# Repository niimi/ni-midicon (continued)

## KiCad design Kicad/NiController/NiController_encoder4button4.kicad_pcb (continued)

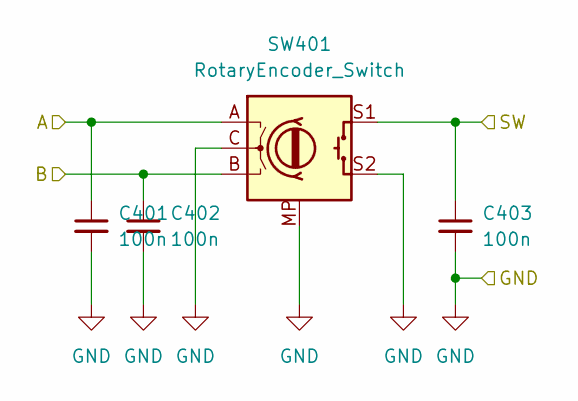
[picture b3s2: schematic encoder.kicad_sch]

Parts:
C401, C402, C403: 100n; C_0603_1608Metric
SW401: RotaryEncoder_Switch; PEC11-4xxxF-Sxxxx

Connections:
/encoder4button4/0_GPA0: C401.1, SW401.A; also elsewhere on the board
/encoder4button4/0_GPA1: C402.1, SW401.B; also elsewhere on the board
/encoder4button4/0_GPA2: C403.1, SW401.S1; also elsewhere on the board
GND: C401.2, C402.2, C403.2, SW401.C, SW401.MP, SW401.S2; also elsewhere on the board

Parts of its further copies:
C501, C502, C503, C601, C602, C603, C701, C702, C703: 100n; C_0603_1608Metric
SW501, SW601, SW701: RotaryEncoder_Switch; PEC11-4xxxF-Sxxxx

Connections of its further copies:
/encoder4button4/0_GPA3: C501.1, SW501.A; also elsewhere on the board
/encoder4button4/0_GPA4: C502.1, SW501.B; also elsewhere on the board
/encoder4button4/0_GPA5: C503.1, SW501.S1; also elsewhere on the board
/encoder4button4/0_GPA6: C601.1, SW601.A; also elsewhere on the board
/encoder4button4/0_GPA7: C602.1, SW601.B; also elsewhere on the board
/encoder4button4/0_GPB0: C603.1, SW601.S1; also elsewhere on the board
/encoder4button4/0_GPB1: C701.1, SW701.A; also elsewhere on the board
/encoder4button4/0_GPB2: C702.1, SW701.B; also elsewhere on the board
/encoder4button4/0_GPB3: C703.1, SW701.S1; also elsewhere on the board
GND: C501.2, C502.2, C503.2, C601.2, C602.2, C603.2, C701.2, C702.2, C703.2, SW501.C, SW501.MP, SW501.S2, SW601.C, SW601.MP, SW601.S2, SW701.C, SW701.MP, SW701.S2; also elsewhere on the board

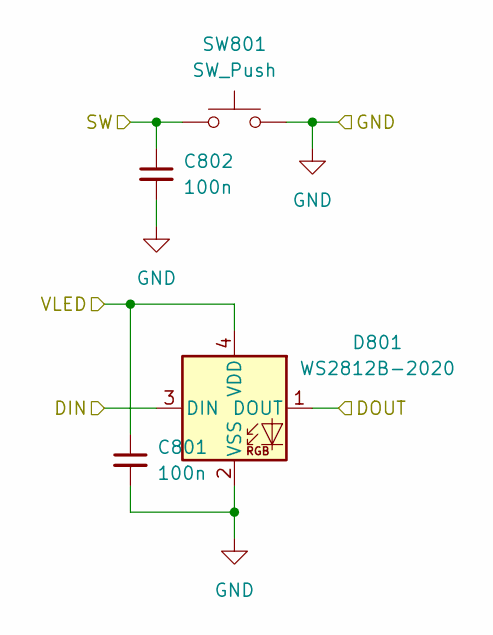
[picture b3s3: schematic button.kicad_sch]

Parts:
C801, C802: 100n; C_0603_1608Metric
D801: WS2812B-2020; LED_WS2812B-2020_PLCC4_2.0x2.0mm
SW801: SW_Push; SW_Cherry_MX_1.00u_PCB

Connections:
/encoder4button4/0_GPB4: C802.1, SW801.1; also elsewhere on the board
/encoder4button4/LED_5V: C801.1, D801.4 (VDD); also elsewhere on the board
/encoder4button4/LED_RING_DOUT: D801.3 (DIN); also elsewhere on the board
/encoder4button4/button0/DOUT: D801.1 (DOUT); also elsewhere on the board
GND: C801.2, C802.2, D801.2 (VSS), SW801.2; also elsewhere on the board

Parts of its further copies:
C901, C902, C1901, C1902, C2901, C2902: 100n; C_0603_1608Metric
D901, D1901, D2901: WS2812B-2020; LED_WS2812B-2020_PLCC4_2.0x2.0mm
SW901, SW1901, SW2901: SW_Push; SW_Cherry_MX_1.00u_PCB

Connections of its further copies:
/encoder4button4/0_GPB5: C902.1, SW901.1; also elsewhere on the board
/encoder4button4/0_GPB6: C1902.1, SW1901.1; also elsewhere on the board
/encoder4button4/0_GPB7: C2902.1, SW2901.1; also elsewhere on the board
/encoder4button4/LED_5V: C901.1, C1901.1, C2901.1, D901.4 (VDD), D1901.4 (VDD), D2901.4 (VDD); also elsewhere on the board
/encoder4button4/LED_DOUT: D2901.1 (DOUT); also elsewhere on the board
/encoder4button4/button0/DOUT: D901.3 (DIN); also elsewhere on the board
/encoder4button4/button1/DOUT: D901.1 (DOUT), D1901.3 (DIN)
/encoder4button4/button2/DOUT: D1901.1 (DOUT), D2901.3 (DIN)
GND: C901.2, C902.2, C1901.2, C1902.2, C2901.2, C2902.2, D901.2 (VSS), D1901.2 (VSS), D2901.2 (VSS), SW901.2, SW1901.2, SW2901.2; also elsewhere on the board

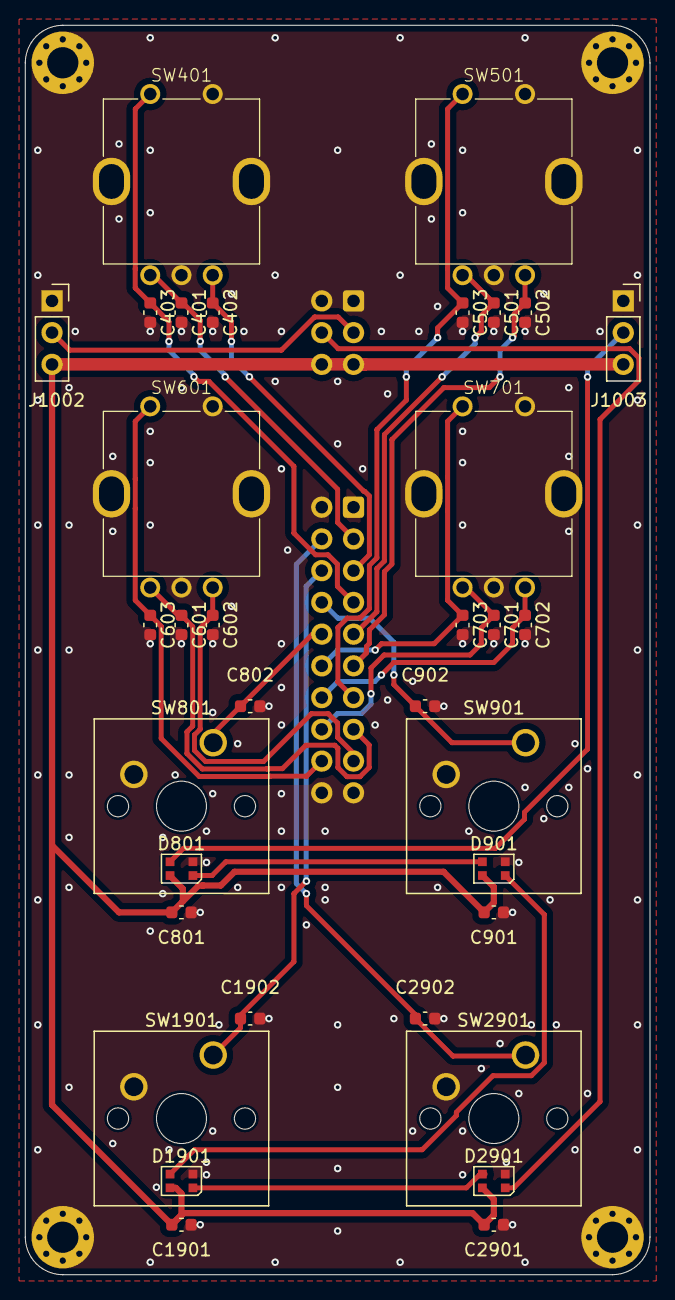
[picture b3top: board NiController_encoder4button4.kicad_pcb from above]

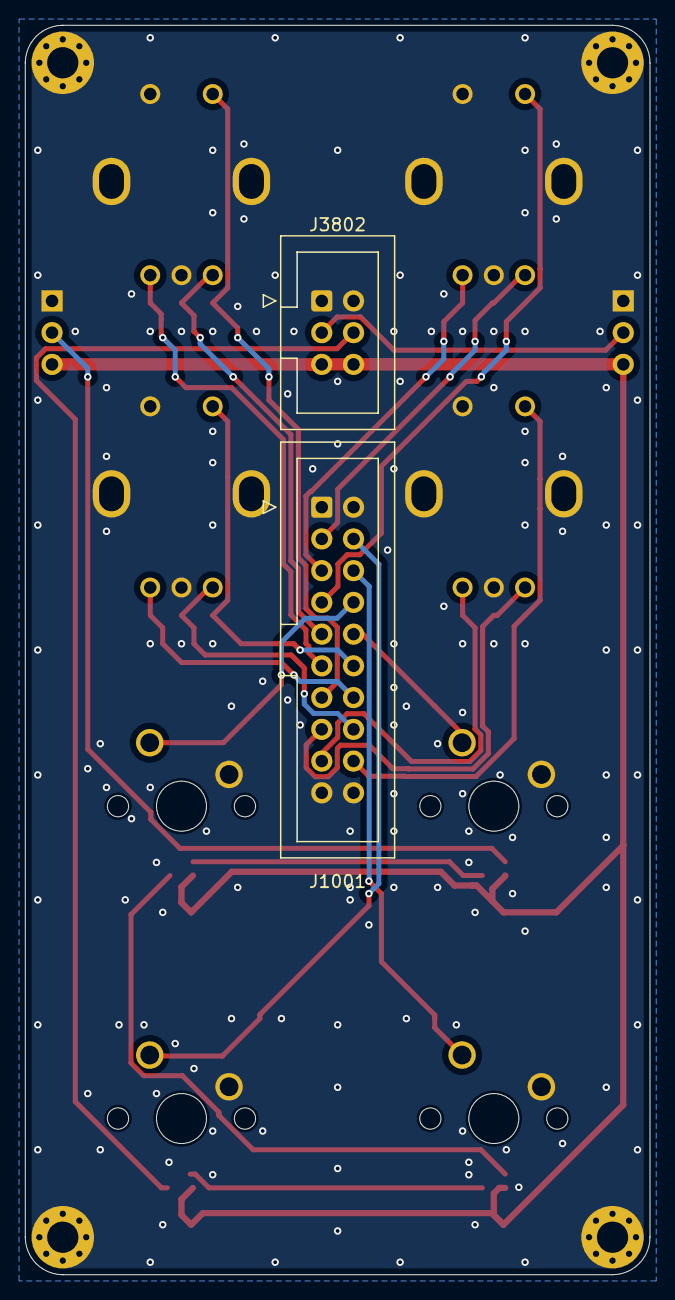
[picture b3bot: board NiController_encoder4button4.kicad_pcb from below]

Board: 2 copper layers, 50.0 x 100.0 mm, 40 parts (2 on the bottom side), 24 nets.

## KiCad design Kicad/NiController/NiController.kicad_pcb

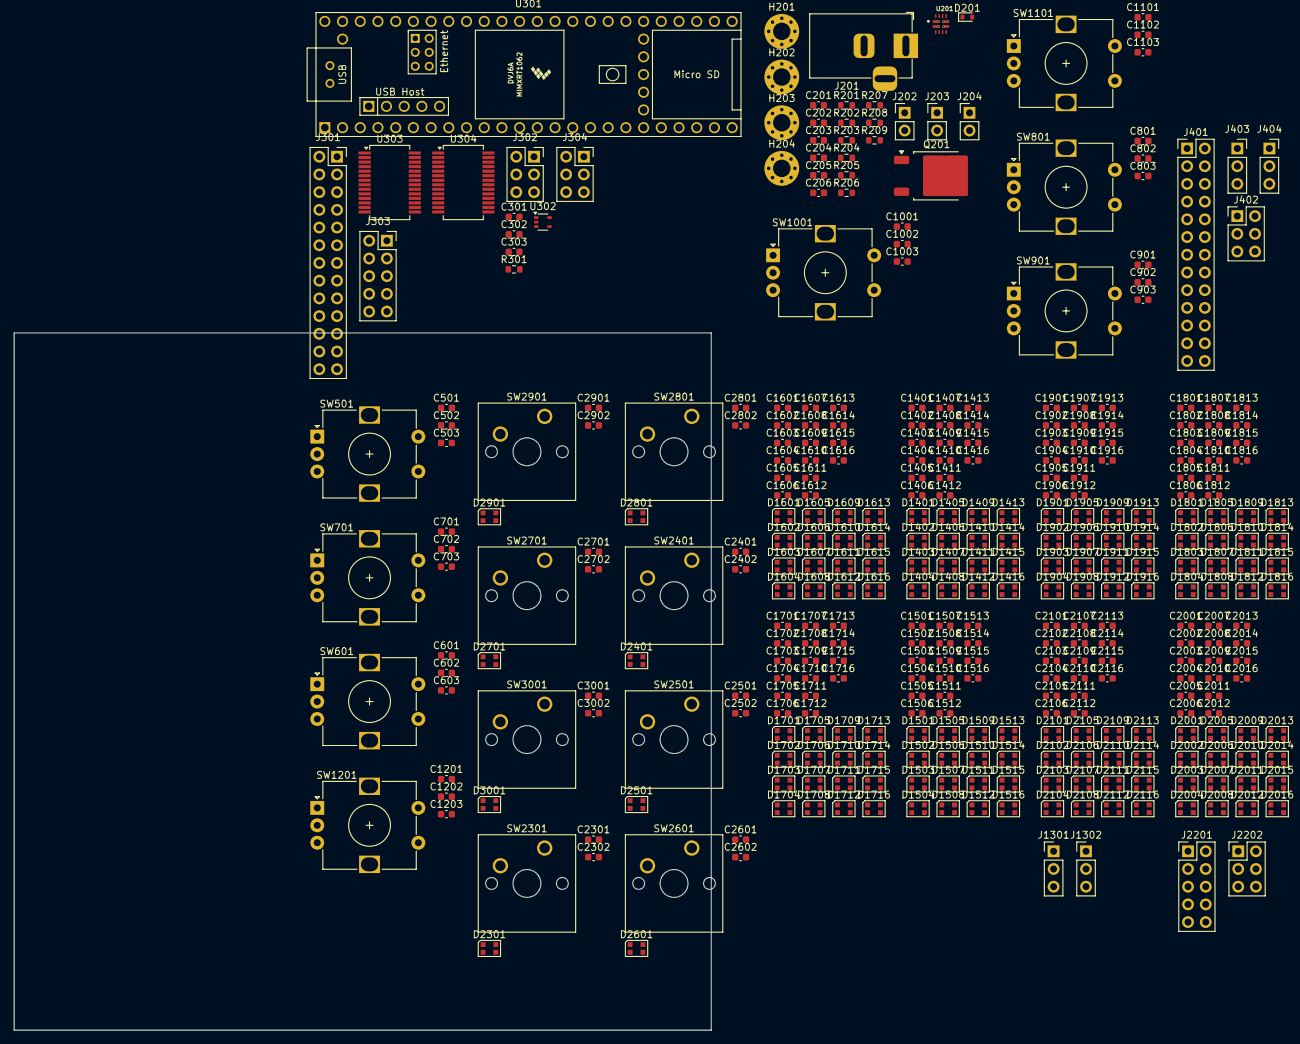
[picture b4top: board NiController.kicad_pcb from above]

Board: 2 copper layers, 100.0 x 100.0 mm, 366 parts (0 on the bottom side), 229 nets, no tracks yet.

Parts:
C201, C206: 1u; C_0603_1608Metric
C202, C203, C204, C205, C301, C302, C303, C501, C502, C503, C601, C602, C603, C701, C702, C703, C801, C802, C803, C901, C902, C903, C1001, C1002, C1003, C1101, C1102, C1103, C1201, C1202, C1203, C1401, C1402, C1403, C1404, C1405, C1406, C1407, C1408, C1409, C1410, C1411, C1412, C1413, C1414, C1415, C1416, C1501, C1502, C1503, C1504, C1505, C1506, C1507, C1508, C1509, C1510, C1511, C1512, C1513, C1514, C1515, C1516, C1601, C1602, C1603, C1604, C1605, C1606, C1607, C1608, C1609, C1610, C1611, C1612, C1613, C1614, C1615, C1616, C1701, C1702, C1703, C1704, C1705, C1706, C1707, C1708, C1709, C1710, C1711, C1712, C1713, C1714, C1715, C1716, C1801, C1802, C1803, C1804, C1805, C1806, C1807, C1808, C1809, C1810, C1811, C1812, C1813, C1814, C1815, C1816, C1901, C1902, C1903, C1904, C1905, C1906, C1907, C1908, C1909, C1910, C1911, C1912, C1913, C1914, C1915, C1916, C2001, C2002, C2003, C2004, C2005, C2006, C2007, C2008, C2009, C2010, C2011, C2012, C2013, C2014, C2015, C2016, C2101, C2102, C2103, C2104, C2105, C2106, C2107, C2108, C2109, C2110, C2111, C2112, C2113, C2114, C2115, C2116, C2301, C2302, C2401, C2402, C2501, C2502, C2601, C2602, C2701, C2702, C2801, C2802, C2901, C2902, C3001, C3002: 100n; C_0603_1608Metric
D201: D_TVS_Small; D_SOD-523
D1401, D1402, D1403, D1404, D1405, D1406, D1407, D1408, D1409, D1410, D1411, D1412, D1413, D1414, D1415, D1416, D1501, D1502, D1503, D1504, D1505, D1506, D1507, D1508, D1509, D1510, D1511, D1512, D1513, D1514, D1515, D1516, D1601, D1602, D1603, D1604, D1605, D1606, D1607, D1608, D1609, D1610, D1611, D1612, D1613, D1614, D1615, D1616, D1701, D1702, D1703, D1704, D1705, D1706, D1707, D1708, D1709, D1710, D1711, D1712, D1713, D1714, D1715, D1716, D1801, D1802, D1803, D1804, D1805, D1806, D1807, D1808, D1809, D1810, D1811, D1812, D1813, D1814, D1815, D1816, D1901, D1902, D1903, D1904, D1905, D1906, D1907, D1908, D1909, D1910, D1911, D1912, D1913, D1914, D1915, D1916, D2001, D2002, D2003, D2004, D2005, D2006, D2007, D2008, D2009, D2010, D2011, D2012, D2013, D2014, D2015, D2016, D2101, D2102, D2103, D2104, D2105, D2106, D2107, D2108, D2109, D2110, D2111, D2112, D2113, D2114, D2115, D2116, D2301, D2401, D2501, D2601, D2701, D2801, D2901, D3001: WS2812B-2020; LED_WS2812B-2020_PLCC4_2.0x2.0mm
H201, H202, H203, H204: MountingHole_Pad; MountingHole_2.5mm_Pad_Via
J201: Barrel_Jack_Switch; BarrelJack_Horizontal
J202, J203, J204: Conn_01x02; PinHeader_1x02_P2.54mm_Vertical
J301: Conn_02x13_Odd_Even; PinSocket_2x13_P2.54mm_Vertical
J302, J304: Conn_02x03_Odd_Even; PinSocket_2x03_P2.54mm_Vertical
J303: Conn_02x05_Odd_Even; PinSocket_2x05_P2.54mm_Vertical
J401: Conn_02x13_Odd_Even; PinHeader_2x13_P2.54mm_Vertical
J402, J2202: Conn_02x03_Odd_Even; PinHeader_2x03_P2.54mm_Vertical
J403, J404: Conn_01x03; PinSocket_1x03_P2.54mm_Vertical
J1301, J1302: Conn_01x03; PinHeader_1x03_P2.54mm_Vertical
J2201: Conn_02x05_Odd_Even; PinHeader_2x05_P2.54mm_Vertical
Q201: Q_PMOS_GDS; TO-252-2
R201, R203: 20.5k; R_0603_1608Metric
R202, R204, R206, R208: 5k; R_0603_1608Metric
R205: 10k; R_0603_1608Metric
R207: 15k; R_0603_1608Metric
R209: 22.1k; R_0603_1608Metric
R301: 100; R_0603_1608Metric
SW501, SW601, SW701, SW801, SW901, SW1001, SW1101, SW1201: RotaryEncoder_Switch; RotaryEncoder_Alps_EC12E-Switch_Vertical_H20mm
SW2301, SW2401, SW2501, SW2601, SW2701, SW2801, SW2901, SW3001: SW_Push; SW_Cherry_MX_1.00u_PCB
U201: TPS2121RUXR; IC_TPS2121RUXR
U301: Teensy4.1; Teensy41
U302: 74LVC1GU04; SOT-353_SC-70-5
U303, U304: MCP23S17_SS; SSOP-28_5.3x10.2mm_P0.65mm

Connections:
+5V: C1401.1, C1402.1, C1403.1, C1404.1, C1405.1, C1406.1, C1407.1, C1408.1, C1409.1, C1410.1, C1411.1, C1412.1, C1413.1, C1414.1, C1415.1, C1416.1, C1501.1, C1502.1, C1503.1, C1504.1, C1505.1, C1506.1, C1507.1, C1508.1, C1509.1, C1510.1, C1511.1, C1512.1, C1513.1, C1514.1, C1515.1, C1516.1, C1601.1, C1602.1, C1603.1, C1604.1, C1605.1, C1606.1, C1607.1, C1608.1, C1609.1, C1610.1, C1611.1, C1612.1, C1613.1, C1614.1, C1615.1, C1616.1, C1701.1, C1702.1, C1703.1, C1704.1, C1705.1, C1706.1, C1707.1, C1708.1, C1709.1, C1710.1, C1711.1, C1712.1, C1713.1, C1714.1, C1715.1, C1716.1, C1801.1, C1802.1, C1803.1, C1804.1, C1805.1, C1806.1, C1807.1, C1808.1, C1809.1, C1810.1, C1811.1, C1812.1, C1813.1, C1814.1, C1815.1, C1816.1, C1901.1, C1902.1, C1903.1, C1904.1, C1905.1, C1906.1, C1907.1, C1908.1, C1909.1, C1910.1, C1911.1, C1912.1, C1913.1, C1914.1, C1915.1, C1916.1, C2001.1, C2002.1, C2003.1, C2004.1, C2005.1, C2006.1, C2007.1, C2008.1, C2009.1, C2010.1, C2011.1, C2012.1, C2013.1, C2014.1, C2015.1, C2016.1, C2101.1, C2102.1, C2103.1, C2104.1, C2105.1, C2106.1, C2107.1, C2108.1, C2109.1, C2110.1, C2111.1, C2112.1, C2113.1, C2114.1, C2115.1, C2116.1, D1401.4 (VDD), D1402.4 (VDD), D1403.4 (VDD), D1404.4 (VDD), D1405.4 (VDD), D1406.4 (VDD), D1407.4 (VDD), D1408.4 (VDD), D1409.4 (VDD), D1410.4 (VDD), D1411.4 (VDD), D1412.4 (VDD), D1413.4 (VDD), D1414.4 (VDD), D1415.4 (VDD), D1416.4 (VDD), D1501.4 (VDD), D1502.4 (VDD), D1503.4 (VDD), D1504.4 (VDD), D1505.4 (VDD), D1506.4 (VDD), D1507.4 (VDD), D1508.4 (VDD), D1509.4 (VDD), D1510.4 (VDD), D1511.4 (VDD), D1512.4 (VDD), D1513.4 (VDD), D1514.4 (VDD), D1515.4 (VDD), D1516.4 (VDD), D1601.4 (VDD), D1602.4 (VDD), D1603.4 (VDD), D1604.4 (VDD), D1605.4 (VDD), D1606.4 (VDD), D1607.4 (VDD), D1608.4 (VDD), D1609.4 (VDD), D1610.4 (VDD), D1611.4 (VDD), D1612.4 (VDD), D1613.4 (VDD), D1614.4 (VDD), D1615.4 (VDD), D1616.4 (VDD), D1701.4 (VDD), D1702.4 (VDD), D1703.4 (VDD), D1704.4 (VDD), D1705.4 (VDD), D1706.4 (VDD), D1707.4 (VDD), D1708.4 (VDD), D1709.4 (VDD), D1710.4 (VDD), D1711.4 (VDD), D1712.4 (VDD), D1713.4 (VDD), D1714.4 (VDD), D1715.4 (VDD), D1716.4 (VDD), D1801.4 (VDD), D1802.4 (VDD), D1803.4 (VDD), D1804.4 (VDD), D1805.4 (VDD), D1806.4 (VDD), D1807.4 (VDD), D1808.4 (VDD), D1809.4 (VDD), D1810.4 (VDD), D1811.4 (VDD), D1812.4 (VDD), D1813.4 (VDD), D1814.4 (VDD), D1815.4 (VDD), D1816.4 (VDD), D1901.4 (VDD), D1902.4 (VDD), D1903.4 (VDD), D1904.4 (VDD), D1905.4 (VDD), D1906.4 (VDD), D1907.4 (VDD), D1908.4 (VDD), D1909.4 (VDD), D1910.4 (VDD), D1911.4 (VDD), D1912.4 (VDD), D1913.4 (VDD), D1914.4 (VDD), D1915.4 (VDD), D1916.4 (VDD), D2001.4 (VDD), D2002.4 (VDD), D2003.4 (VDD), D2004.4 (VDD), D2005.4 (VDD), D2006.4 (VDD), D2007.4 (VDD), D2008.4 (VDD), D2009.4 (VDD), D2010.4 (VDD), D2011.4 (VDD), D2012.4 (VDD), D2013.4 (VDD), D2014.4 (VDD), D2015.4 (VDD), D2016.4 (VDD), D2101.4 (VDD), D2102.4 (VDD), D2103.4 (VDD), D2104.4 (VDD), D2105.4 (VDD), D2106.4 (VDD), D2107.4 (VDD), D2108.4 (VDD), D2109.4 (VDD), D2110.4 (VDD), D2111.4 (VDD), D2112.4 (VDD), D2113.4 (VDD), D2114.4 (VDD), D2115.4 (VDD), D2116.4 (VDD), J1301.3, J1302.3
/button8/1_GPB0: C2302.1, J2201.3, SW2301.1
/button8/1_GPB1: C2402.1, J2201.4, SW2401.1
/button8/1_GPB2: C2502.1, J2201.5, SW2501.1
/button8/1_GPB3: C2602.1, J2201.6, SW2601.1
/button8/1_GPB4: C2702.1, J2201.7, SW2701.1
/button8/1_GPB5: C2802.1, J2201.8, SW2801.1
/button8/1_GPB6: C2902.1, J2201.9, SW2901.1
/button8/1_GPB7: C3002.1, J2201.10, SW3001.1
/button8/LED_5V: C2301.1, C2401.1, C2501.1, C2601.1, C2701.1, C2801.1, C2901.1, C3001.1, D2301.4 (VDD), D2401.4 (VDD), D2501.4 (VDD), D2601.4 (VDD), D2701.4 (VDD), D2801.4 (VDD), D2901.4 (VDD), D3001.4 (VDD), J2202.5, J2202.6
/button8/LED_DIN: D2301.3 (DIN), J2202.3
/button8/LED_DOUT: D3001.1 (DOUT), J2202.4
/button8/button1/DOUT: D2401.1 (DOUT), D2501.3 (DIN)
/button8/button2/DOUT: D2501.1 (DOUT), D2601.3 (DIN)
/button8/button3/DOUT: D2601.1 (DOUT), D2701.3 (DIN)
/button8/button4/DOUT: D2701.1 (DOUT), D2801.3 (DIN)
/button8/button5/DOUT: D2801.1 (DOUT), D2901.3 (DIN)
/button8/button6/DOUT: D2901.1 (DOUT), D3001.3 (DIN)
/button8/button/DOUT: D2301.1 (DOUT), D2401.3 (DIN)
/encoder8/0_GPA0: C501.1, J401.3, SW501.A
/encoder8/0_GPA1: C601.1, J401.6, SW601.A
/encoder8/0_GPA2: C701.1, J401.9, SW701.A
/encoder8/0_GPA3: C801.1, J401.12, SW801.A
/encoder8/0_GPA4: C901.1, J401.15, SW901.A
/encoder8/0_GPA5: C1001.1, J401.18, SW1001.A
/encoder8/0_GPA6: C1101.1, J401.21, SW1101.A
/encoder8/0_GPA7: C1201.1, J401.24, SW1201.A
/encoder8/0_GPB0: C502.1, J401.4, SW501.B
/encoder8/0_GPB1: C602.1, J401.7, SW601.B
/encoder8/0_GPB2: C702.1, J401.10, SW701.B
/encoder8/0_GPB3: C802.1, J401.13, SW801.B
/encoder8/0_GPB4: C902.1, J401.16, SW901.B
/encoder8/0_GPB5: C1002.1, J401.19, SW1001.B
/encoder8/0_GPB6: C1102.1, J401.22, SW1101.B
/encoder8/0_GPB7: C1202.1, J401.25, SW1201.B
/encoder8/1_GPA0: C503.1, J401.5, SW501.S1
/encoder8/1_GPA1: C603.1, J401.8, SW601.S1
/encoder8/1_GPA2: C703.1, J401.11, SW701.S1
/encoder8/1_GPA3: C803.1, J401.14, SW801.S1
/encoder8/1_GPA4: C903.1, J401.17, SW901.S1
/encoder8/1_GPA5: C1003.1, J401.20, SW1001.S1
/encoder8/1_GPA6: C1103.1, J401.23, SW1101.S1
/encoder8/1_GPA7: C1203.1, J401.26, SW1201.S1
/encoder8/LED_5V: J402.5, J402.6, J403.3, J404.3
/encoder8/LED_DIN: J402.3, J403.2
/encoder8/LED_DOUT: J402.4, J404.2
/ledRing8/DIN: D1401.3 (DIN), J1301.2
/ledRing8/DOUT: D2116.1 (DOUT), J1302.2
/ledRing8/ledRing1/DIN: D1501.3 (DIN), D1616.1 (DOUT)
/ledRing8/ledRing1/DOUT: D1516.1 (DOUT), D1701.3 (DIN)
/ledRing8/ledRing3/DOUT: D1716.1 (DOUT), D1801.3 (DIN)
/ledRing8/ledRing4/DOUT: D1816.1 (DOUT), D1901.3 (DIN)
/ledRing8/ledRing5/DOUT: D1916.1 (DOUT), D2001.3 (DIN)
/ledRing8/ledRing6/DOUT: D2016.1 (DOUT), D2101.3 (DIN)
/ledRing8/ledRing/DOUT: D1416.1 (DOUT), D1601.3 (DIN)
/main/ST: U201.9 (ST), U301.5 (3_LRCLK2)
/main/Teensy/0_GPA0: J301.3, U303.21 (GPA0)
/main/Teensy/0_GPA1: J301.6, U303.22 (GPA1)
/main/Teensy/0_GPA2: J301.9, U303.23 (GPA2)
/main/Teensy/0_GPA3: J301.12, U303.24 (GPA3)
/main/Teensy/0_GPA4: J301.15, U303.25 (GPA4)
/main/Teensy/0_GPA5: J301.18, U303.26 (GPA5)
/main/Teensy/0_GPA6: J301.21, U303.27 (GPA6)
/main/Teensy/0_GPA7: J301.24, U303.28 (GPA7)
/main/Teensy/0_GPB0: J301.4, U303.1 (GPB0)
/main/Teensy/0_GPB1: J301.7, U303.2 (GPB1)
/main/Teensy/0_GPB2: J301.10, U303.3 (GPB2)
/main/Teensy/0_GPB3: J301.13, U303.4 (GPB3)
/main/Teensy/0_GPB4: J301.16, U303.5 (GPB4)
/main/Teensy/0_GPB5: J301.19, U303.6 (GPB5)
/main/Teensy/0_GPB6: J301.22, U303.7 (GPB6)
/main/Teensy/0_GPB7: J301.25, U303.8 (GPB7)
/main/Teensy/1_GPA0: J301.5, U304.21 (GPA0)
/main/Teensy/1_GPA1: J301.8, U304.22 (GPA1)
/main/Teensy/1_GPA2: J301.11, U304.23 (GPA2)
/main/Teensy/1_GPA3: J301.14, U304.24 (GPA3)
/main/Teensy/1_GPA4: J301.17, U304.25 (GPA4)
/main/Teensy/1_GPA5: J301.20, U304.26 (GPA5)
/main/Teensy/1_GPA6: J301.23, U304.27 (GPA6)
/main/Teensy/1_GPA7: J301.26, U304.28 (GPA7)
/main/Teensy/1_GPB0: J303.3, U304.1 (GPB0)
/main/Teensy/1_GPB1: J303.4, U304.2 (GPB1)
/main/Teensy/1_GPB2: J303.5, U304.3 (GPB2)
/main/Teensy/1_GPB3: J303.6, U304.4 (GPB3)
/main/Teensy/1_GPB4: J303.7, U304.5 (GPB4)
/main/Teensy/1_GPB5: J303.8, U304.6 (GPB5)
/main/Teensy/1_GPB6: J303.9, U304.7 (GPB6)
/main/Teensy/1_GPB7: J303.10, U304.8 (GPB7)
/main/Teensy/3.3V: C302.2, C303.2, U301.46 (3V3), U303.9 (VDD), U304.9 (VDD), U304.15 (A0)
/main/Teensy/MCP_CS: U301.12 (10_CS_MQSR), U303.11 (~CS), U304.11 (~CS)
/main/Teensy/MCP_MISO: U301.14 (12_MISO_MQSL), U303.14 (SO), U304.14 (SO)
/main/Teensy/MCP_MOSI: U301.13 (11_MOSI_CTX1), U303.13 (SI), U304.13 (SI)
/main/Teensy/MCP_RST: U301.6 (4_BCLK2), U303.18 (~RESET), U304.18 (~RESET)
/main/Teensy/MCP_SCK: U301.35 (13_SCK_LED), U303.12 (SCK), U304.12 (SCK)
/main/Teensy/NEOPIXEL_DATA: U301.4 (2_OUT2), U302.2
/main/Teensy/NEOPIXEL_DATA_5V: J302.3, R301.2
/main/VAUX: C201.1, C202.1, J202.2, Q201.3 (S), R201.1, R205.1, U201.7 (IN1), U201.7_1 (IN1)
/main/VCC: C205.1, C301.1, J204.2, J302.5, J302.6, J304.5, J304.6, U201.1 (OUT), U201.1_1 (OUT), U201.8 (OUT), U201.8_1 (OUT), U301.48 (VIN), U302.5 (VCC)
/main/VUSB: C203.1, C206.1, J203.2, R203.1, R207.1, U201.2 (IN2), U201.2_1 (IN2), U301.49 (VUSB)
GND: C201.2, C202.2, C203.2, C204.2, C205.2, C206.2, C301.2, C302.1, C303.1, C501.2, C502.2, C503.2, C601.2, C602.2, C603.2, C701.2, C702.2, C703.2, C801.2, C802.2, C803.2, C901.2, C902.2, C903.2, C1001.2, C1002.2, C1003.2, C1101.2, C1102.2, C1103.2, C1201.2, C1202.2, C1203.2, C1401.2, C1402.2, C1403.2, C1404.2, C1405.2, C1406.2, C1407.2, C1408.2, C1409.2, C1410.2, C1411.2, C1412.2, C1413.2, C1414.2, C1415.2, C1416.2, C1501.2, C1502.2, C1503.2, C1504.2, C1505.2, C1506.2, C1507.2, C1508.2, C1509.2, C1510.2, C1511.2, C1512.2, C1513.2, C1514.2, C1515.2, C1516.2, C1601.2, C1602.2, C1603.2, C1604.2, C1605.2, C1606.2, C1607.2, C1608.2, C1609.2, C1610.2, C1611.2, C1612.2, C1613.2, C1614.2, C1615.2, C1616.2, C1701.2, C1702.2, C1703.2, C1704.2, C1705.2, C1706.2, C1707.2, C1708.2, C1709.2, C1710.2, C1711.2, C1712.2, C1713.2, C1714.2, C1715.2, C1716.2, C1801.2, C1802.2, C1803.2, C1804.2, C1805.2, C1806.2, C1807.2, C1808.2, C1809.2, C1810.2, C1811.2, C1812.2, C1813.2, C1814.2, C1815.2, C1816.2, C1901.2, C1902.2, C1903.2, C1904.2, C1905.2, C1906.2, C1907.2, C1908.2, C1909.2, C1910.2, C1911.2, C1912.2, C1913.2, C1914.2, C1915.2, C1916.2, C2001.2, C2002.2, C2003.2, C2004.2, C2005.2, C2006.2, C2007.2, C2008.2, C2009.2, C2010.2, C2011.2, C2012.2, C2013.2, C2014.2, C2015.2, C2016.2, C2101.2, C2102.2, C2103.2, C2104.2, C2105.2, C2106.2, C2107.2, C2108.2, C2109.2, C2110.2, C2111.2, C2112.2, C2113.2, C2114.2, C2115.2, C2116.2, C2301.2, C2302.2, C2401.2, C2402.2, C2501.2, C2502.2, C2601.2, C2602.2, C2701.2, C2702.2, C2801.2, C2802.2, C2901.2, C2902.2, C3001.2, C3002.2, D201.1 (A1), D1401.2 (VSS), D1402.2 (VSS), D1403.2 (VSS), D1404.2 (VSS), D1405.2 (VSS), D1406.2 (VSS), D1407.2 (VSS), D1408.2 (VSS), D1409.2 (VSS), D1410.2 (VSS), D1411.2 (VSS), D1412.2 (VSS), D1413.2 (VSS), D1414.2 (VSS), D1415.2 (VSS), D1416.2 (VSS), D1501.2 (VSS), D1502.2 (VSS), D1503.2 (VSS), D1504.2 (VSS), D1505.2 (VSS), D1506.2 (VSS), D1507.2 (VSS), D1508.2 (VSS), D1509.2 (VSS), D1510.2 (VSS), D1511.2 (VSS), D1512.2 (VSS), D1513.2 (VSS), D1514.2 (VSS), D1515.2 (VSS), D1516.2 (VSS), D1601.2 (VSS), D1602.2 (VSS), D1603.2 (VSS), D1604.2 (VSS), D1605.2 (VSS), D1606.2 (VSS), D1607.2 (VSS), D1608.2 (VSS), D1609.2 (VSS), D1610.2 (VSS), D1611.2 (VSS), D1612.2 (VSS), D1613.2 (VSS), D1614.2 (VSS), D1615.2 (VSS), D1616.2 (VSS), D1701.2 (VSS), D1702.2 (VSS), D1703.2 (VSS), D1704.2 (VSS), D1705.2 (VSS), D1706.2 (VSS), D1707.2 (VSS), D1708.2 (VSS), D1709.2 (VSS), D1710.2 (VSS), D1711.2 (VSS), D1712.2 (VSS), D1713.2 (VSS), D1714.2 (VSS), D1715.2 (VSS), D1716.2 (VSS), D1801.2 (VSS), D1802.2 (VSS), D1803.2 (VSS), D1804.2 (VSS), D1805.2 (VSS), D1806.2 (VSS), D1807.2 (VSS), D1808.2 (VSS), D1809.2 (VSS), D1810.2 (VSS), D1811.2 (VSS), D1812.2 (VSS), D1813.2 (VSS), D1814.2 (VSS), D1815.2 (VSS), D1816.2 (VSS), D1901.2 (VSS), D1902.2 (VSS), D1903.2 (VSS), D1904.2 (VSS), D1905.2 (VSS), D1906.2 (VSS), D1907.2 (VSS), D1908.2 (VSS), D1909.2 (VSS), D1910.2 (VSS), D1911.2 (VSS), D1912.2 (VSS), D1913.2 (VSS), D1914.2 (VSS), D1915.2 (VSS), D1916.2 (VSS), D2001.2 (VSS), D2002.2 (VSS), D2003.2 (VSS), D2004.2 (VSS), D2005.2 (VSS), D2006.2 (VSS), D2007.2 (VSS), D2008.2 (VSS), D2009.2 (VSS), D2010.2 (VSS), D2011.2 (VSS), D2012.2 (VSS), D2013.2 (VSS), D2014.2 (VSS), D2015.2 (VSS), D2016.2 (VSS), D2101.2 (VSS), D2102.2 (VSS), D2103.2 (VSS), D2104.2 (VSS), D2105.2 (VSS), D2106.2 (VSS), D2107.2 (VSS), D2108.2 (VSS), D2109.2 (VSS), D2110.2 (VSS), D2111.2 (VSS), D2112.2 (VSS), D2113.2 (VSS), D2114.2 (VSS), D2115.2 (VSS), D2116.2 (VSS), D2301.2 (VSS), D2401.2 (VSS), D2501.2 (VSS), D2601.2 (VSS), D2701.2 (VSS), D2801.2 (VSS), D2901.2 (VSS), D3001.2 (VSS), H201.1, H202.1, H203.1, H204.1, J201.2, J201.3, J202.1, J203.1, J204.1, J301.1, J301.2, J302.1, J302.2, J303.1, J303.2, J304.1, J304.2, J401.1, J401.2, J402.1, J402.2, J403.1, J404.1, J1301.1, J1302.1, J2201.1, J2201.2, J2202.1, J2202.2, Q201.1 (G), R202.2, R204.2, R206.2, R208.2, R209.2, SW501.C, SW501.MP, SW501.S2, SW601.C, SW601.MP, SW601.S2, SW701.C, SW701.MP, SW701.S2, SW801.C, SW801.MP, SW801.S2, SW901.C, SW901.MP, SW901.S2, SW1001.C, SW1001.MP, SW1001.S2, SW1101.C, SW1101.MP, SW1101.S2, SW1201.C, SW1201.MP, SW1201.S2, SW2301.2, SW2401.2, SW2501.2, SW2601.2, SW2701.2, SW2801.2, SW2901.2, SW3001.2, U201.12 (GND), U302.3 (GND), U303.10 (VSS), U303.15 (A0), U303.16 (A1), U303.17 (A2), U304.10 (VSS), U304.16 (A1), U304.17 (A2)
unnamed: D201.2 (A2), J201.1, Q201.2 (D)
unnamed: D1401.1 (DOUT), D1402.3 (DIN)
unnamed: D1402.1 (DOUT), D1403.3 (DIN)
unnamed: D1403.1 (DOUT), D1404.3 (DIN)
unnamed: D1404.1 (DOUT), D1405.3 (DIN)
unnamed: D1405.1 (DOUT), D1406.3 (DIN)
unnamed: D1406.1 (DOUT), D1407.3 (DIN)
unnamed: D1407.1 (DOUT), D1408.3 (DIN)
unnamed: D1408.1 (DOUT), D1409.3 (DIN)
unnamed: D1409.1 (DOUT), D1410.3 (DIN)
unnamed: D1410.1 (DOUT), D1411.3 (DIN)
unnamed: D1411.1 (DOUT), D1412.3 (DIN)
unnamed: D1412.1 (DOUT), D1413.3 (DIN)
unnamed: D1413.1 (DOUT), D1414.3 (DIN)
unnamed: D1414.1 (DOUT), D1415.3 (DIN)
unnamed: D1415.1 (DOUT), D1416.3 (DIN)
unnamed: D1501.1 (DOUT), D1502.3 (DIN)
unnamed: D1502.1 (DOUT), D1503.3 (DIN)
unnamed: D1503.1 (DOUT), D1504.3 (DIN)
unnamed: D1504.1 (DOUT), D1505.3 (DIN)
unnamed: D1505.1 (DOUT), D1506.3 (DIN)
unnamed: D1506.1 (DOUT), D1507.3 (DIN)
unnamed: D1507.1 (DOUT), D1508.3 (DIN)
unnamed: D1508.1 (DOUT), D1509.3 (DIN)
unnamed: D1509.1 (DOUT), D1510.3 (DIN)
unnamed: D1510.1 (DOUT), D1511.3 (DIN)
unnamed: D1511.1 (DOUT), D1512.3 (DIN)
unnamed: D1512.1 (DOUT), D1513.3 (DIN)
unnamed: D1513.1 (DOUT), D1514.3 (DIN)
unnamed: D1514.1 (DOUT), D1515.3 (DIN)
unnamed: D1515.1 (DOUT), D1516.3 (DIN)
unnamed: D1601.1 (DOUT), D1602.3 (DIN)
unnamed: D1602.1 (DOUT), D1603.3 (DIN)
unnamed: D1603.1 (DOUT), D1604.3 (DIN)
unnamed: D1604.1 (DOUT), D1605.3 (DIN)
unnamed: D1605.1 (DOUT), D1606.3 (DIN)
unnamed: D1606.1 (DOUT), D1607.3 (DIN)
unnamed: D1607.1 (DOUT), D1608.3 (DIN)
unnamed: D1608.1 (DOUT), D1609.3 (DIN)
unnamed: D1609.1 (DOUT), D1610.3 (DIN)
unnamed: D1610.1 (DOUT), D1611.3 (DIN)
unnamed: D1611.1 (DOUT), D1612.3 (DIN)
unnamed: D1612.1 (DOUT), D1613.3 (DIN)
unnamed: D1613.1 (DOUT), D1614.3 (DIN)
unnamed: D1614.1 (DOUT), D1615.3 (DIN)
unnamed: D1615.1 (DOUT), D1616.3 (DIN)
unnamed: D1701.1 (DOUT), D1702.3 (DIN)
unnamed: D1702.1 (DOUT), D1703.3 (DIN)
unnamed: D1703.1 (DOUT), D1704.3 (DIN)
unnamed: D1704.1 (DOUT), D1705.3 (DIN)
unnamed: D1705.1 (DOUT), D1706.3 (DIN)
unnamed: D1706.1 (DOUT), D1707.3 (DIN)
unnamed: D1707.1 (DOUT), D1708.3 (DIN)
unnamed: D1708.1 (DOUT), D1709.3 (DIN)
unnamed: D1709.1 (DOUT), D1710.3 (DIN)
unnamed: D1710.1 (DOUT), D1711.3 (DIN)
unnamed: D1711.1 (DOUT), D1712.3 (DIN)
unnamed: D1712.1 (DOUT), D1713.3 (DIN)
unnamed: D1713.1 (DOUT), D1714.3 (DIN)
unnamed: D1714.1 (DOUT), D1715.3 (DIN)
unnamed: D1715.1 (DOUT), D1716.3 (DIN)
unnamed: D1801.1 (DOUT), D1802.3 (DIN)
unnamed: D1802.1 (DOUT), D1803.3 (DIN)
unnamed: D1803.1 (DOUT), D1804.3 (DIN)
unnamed: D1804.1 (DOUT), D1805.3 (DIN)
unnamed: D1805.1 (DOUT), D1806.3 (DIN)
unnamed: D1806.1 (DOUT), D1807.3 (DIN)
unnamed: D1807.1 (DOUT), D1808.3 (DIN)
unnamed: D1808.1 (DOUT), D1809.3 (DIN)
unnamed: D1809.1 (DOUT), D1810.3 (DIN)
unnamed: D1810.1 (DOUT), D1811.3 (DIN)
unnamed: D1811.1 (DOUT), D1812.3 (DIN)
unnamed: D1812.1 (DOUT), D1813.3 (DIN)
unnamed: D1813.1 (DOUT), D1814.3 (DIN)
unnamed: D1814.1 (DOUT), D1815.3 (DIN)
unnamed: D1815.1 (DOUT), D1816.3 (DIN)
unnamed: D1901.1 (DOUT), D1902.3 (DIN)
unnamed: D1902.1 (DOUT), D1903.3 (DIN)
unnamed: D1903.1 (DOUT), D1904.3 (DIN)
unnamed: D1904.1 (DOUT), D1905.3 (DIN)
unnamed: D1905.1 (DOUT), D1906.3 (DIN)
unnamed: D1906.1 (DOUT), D1907.3 (DIN)
unnamed: D1907.1 (DOUT), D1908.3 (DIN)
unnamed: D1908.1 (DOUT), D1909.3 (DIN)
unnamed: D1909.1 (DOUT), D1910.3 (DIN)
unnamed: D1910.1 (DOUT), D1911.3 (DIN)
unnamed: D1911.1 (DOUT), D1912.3 (DIN)
unnamed: D1912.1 (DOUT), D1913.3 (DIN)
unnamed: D1913.1 (DOUT), D1914.3 (DIN)
unnamed: D1914.1 (DOUT), D1915.3 (DIN)
unnamed: D1915.1 (DOUT), D1916.3 (DIN)
unnamed: D2001.1 (DOUT), D2002.3 (DIN)
unnamed: D2002.1 (DOUT), D2003.3 (DIN)
unnamed: D2003.1 (DOUT), D2004.3 (DIN)
unnamed: D2004.1 (DOUT), D2005.3 (DIN)
unnamed: D2005.1 (DOUT), D2006.3 (DIN)
unnamed: D2006.1 (DOUT), D2007.3 (DIN)
unnamed: D2007.1 (DOUT), D2008.3 (DIN)
unnamed: D2008.1 (DOUT), D2009.3 (DIN)
unnamed: D2009.1 (DOUT), D2010.3 (DIN)
unnamed: D2010.1 (DOUT), D2011.3 (DIN)
unnamed: D2011.1 (DOUT), D2012.3 (DIN)
unnamed: D2012.1 (DOUT), D2013.3 (DIN)
unnamed: D2013.1 (DOUT), D2014.3 (DIN)
unnamed: D2014.1 (DOUT), D2015.3 (DIN)
unnamed: D2015.1 (DOUT), D2016.3 (DIN)
unnamed: D2101.1 (DOUT), D2102.3 (DIN)
unnamed: D2102.1 (DOUT), D2103.3 (DIN)
unnamed: D2103.1 (DOUT), D2104.3 (DIN)
unnamed: D2104.1 (DOUT), D2105.3 (DIN)
unnamed: D2105.1 (DOUT), D2106.3 (DIN)
unnamed: D2106.1 (DOUT), D2107.3 (DIN)
unnamed: D2107.1 (DOUT), D2108.3 (DIN)
unnamed: D2108.1 (DOUT), D2109.3 (DIN)
unnamed: D2109.1 (DOUT), D2110.3 (DIN)
unnamed: D2110.1 (DOUT), D2111.3 (DIN)
unnamed: D2111.1 (DOUT), D2112.3 (DIN)
unnamed: D2112.1 (DOUT), D2113.3 (DIN)
unnamed: D2113.1 (DOUT), D2114.3 (DIN)
unnamed: D2114.1 (DOUT), D2115.3 (DIN)
unnamed: D2115.1 (DOUT), D2116.3 (DIN)
unnamed: J302.4, J304.3
unnamed: R301.1, U302.4
unnamed: R207.2, R208.1, U201.3 (CP2)
unnamed: R209.1, U201.10 (ILIM)
unnamed: R201.2, R202.1, U201.5 (OV1)
unnamed: R203.2, R204.1, U201.4 (OV2)
unnamed: R205.2, R206.1, U201.6 (PR1)
unnamed: C204.1, U201.11 (SS)

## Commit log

2025-08-12 enc4btn4
2025-08-12 led ring 4
2025-08-15 enc btn
2025-08-16 main
